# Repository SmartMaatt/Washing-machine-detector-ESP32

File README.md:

<h1 align="center">
    Alarm Amplifier Project
</h1>

<p align="center">
  <a href="#overview">Overview</a> •
  <a href="#hardware">Hardware</a> •
  <a href="#software">Software</a> •
  <a href="#usage-guide">Usage Guide</a> •
  <a href="#testing-and-troubleshooting">Testing and Troubleshooting</a> •
  <a href="#license">License</a>
</p>

## Overview

This project involves the development of an alarm amplifier system designed to monitor the light status of household appliances using photoresistors. It reacts to changes in light with an audio alarm and Bluetooth console notifications. The system is built around the ESP32 microcontroller, incorporating features like Wi-Fi and Bluetooth connectivity.

## Hardware

### Components

- **ESP32 Microcontroller**: Central processing unit of the system, equipped with Wi-Fi and Bluetooth modules.
- **MAX99357 Audio Amplifier**: Converts digital signals into analog sound for the speaker.
- **Photoresistors**: Detects the light status from household appliances.
- **10kOhm Resistors**: Used in conjunction with the photoresistors to create a voltage divider.
- **B3F-1000S Button**: Manual reset button for the alarm system.

*Hardware Components*

### Circuit Diagram

The following is the circuit diagram of the alarm amplifier system:

*Circuit Diagram*

## Software

### Source Code

The project's source code is written in C and utilizes the Arduino IDE for development. Key libraries include:

- `AudioOutputI2S.h`
- `AudioFileSourcePROGMEM.h`
- `AudioGeneratorFLAC.h`
- `BluetoothSerial.h`

### Main Functionalities

- **Initial Setup**: Initializes the system and sets up Bluetooth and audio configurations.
- **Loop Function**: Manages the reading of sensor data, Bluetooth inputs, and alarm triggering.
- **Alarm Management**: Handles the audio alarm based on sensor input and allows manual reset.

### Bluetooth Commands

- `input1`, `input2`, `input3`: Activate/deactivate specific sensors.
- `ShowData`: Display current sensor data and status.
- `stop`: Stop the current alarm.

## Installation and Setup

To install and set up the software on your ESP32 microcontroller, follow these steps:

1. **Software Requirements**:
   - Ensure you have the latest version of the Arduino IDE installed on your computer. It can be downloaded from the [Arduino website](https://www.arduino.cc/en/software).

2. **ESP32 Board Manager Installation**:
   - Open the Arduino IDE.
   - Go to File > Preferences and in the "Additional Board Manager URLs" field, add the following URL: `https://dl.espressif.com/dl/package_esp32_index.json`.
   - Open the Board Manager by going to Tools > Board > Boards Manager, search for ESP32, and install the latest version.

3. **Connect the ESP32 to Your Computer**:
   - Using a micro USB cable, connect the ESP32 to your computer. Ensure that the ESP32 is powered on.

4. **Select the Correct Board and Port**:
   - In the Arduino IDE, go to Tools > Board and select the appropriate ESP32 board (e.g., ESP32 Dev Module).
   - Go to Tools > Port and select the COM port that the ESP32 is connected to.

5. **Load the Software**:
   - Open the project source code in the Arduino IDE.
   - If any additional libraries are required (as mentioned in the Software section), make sure they are installed.

6. **Compile and Upload**:
   - Click the "Upload" button in the Arduino IDE to compile the code and upload it to the ESP32.
   - Wait for the message "Done uploading" to appear in the IDE's console window.

7. **Verify Operation**:
   - After the code is successfully uploaded, the ESP32 should start running the program.
   - Monitor the Serial Monitor in the Arduino IDE for any debug information or confirmation messages.

8. **Bluetooth Pairing**:
   - On your smartphone or Bluetooth-enabled device, turn on Bluetooth and search for new devices.
   - Find the "Washing Machine Detector" and pair with it.
   - Once paired, you can use Bluetooth terminal applications to send commands to the ESP32.

If you encounter any issues during installation, refer to the Troubleshooting section for guidance.

## Usage Guide

To effectively utilize the alarm amplifier system, follow these steps:

1. **Power Connection**: Connect the system to a power source using the micro USB port on the ESP32.
2. **Mounting**: Attach the system near your chosen appliance, ensuring the photoresistors are positioned to accurately detect the appliance's light status.
3. **Bluetooth Connection**: Use a smartphone or computer with Bluetooth to connect to the system. The default Bluetooth name is "Washing Machine Detector".
4. **Sensor Configuration**: Via the Bluetooth terminal, send commands to activate or deactivate the sensors based on your needs. Use `input1`, `input2`, and `input3` commands to control respective sensors.
5. **Monitoring**: The system will now monitor the light signals from the appliance and trigger the alarm when specific conditions are met.
6. **Responding to Alarms**: When the alarm sounds, indicating the completion of an appliance's cycle, you can turn it off using the manual button on the system or through the Bluetooth command `stop`.
7. **Resetting the System**: After stopping the alarm, the system will reset to its initial state with all sensors deactivated. Reactivate the desired sensors to continue monitoring.

## Testing and Troubleshooting

### Testing Process

1. **Functional Testing**: Each component (microcontroller, audio amplifier, photoresistors) was individually tested for functionality before integration.
2. **Integration Testing**: The complete system was tested to ensure all components worked together seamlessly.
3. **Scenario Testing**: Simulated various appliance statuses (light on/off) to test the system's response and the accuracy of sensor readings.
4. **Usability Testing**: Non-technical users tested the system to ensure user-friendliness and ease of setup and operation.
5. **Longevity Testing**: Operated the system over extended periods to ensure durability and consistent performance.

### Troubleshooting

- **Bluetooth Connectivity Issues**: Ensure the device is within range and the ESP32 is powered correctly. Restart the Bluetooth connection if necessary.
- **False Alarms**: Check the positioning of the photoresistors. Ensure they accurately detect the appliance's light without interference from external light sources.
- **System Not Responding**: Verify the power supply and connections. Check for any loose connections in the circuit.

## Conclusions

1. **Functionality**: The system successfully detects the light status from appliances and triggers an alarm, demonstrating effective integration of hardware and software components.
2. **User-Friendly Design**: Testing with non-technical users highlighted the system's user-friendly design and easy setup process.
3. **Challenges Overcome**: Initially faced challenges with integrating sound playback and Bluetooth connectivity. These were resolved through software modifications, improving the system's reliability.
4. **Technical Skills Enhanced**: Gained significant experience in microprocessor systems, circuit design, and practical problem-solving.
5. **Future Improvements**: Potential enhancements include refining the user interface for Bluetooth control and expanding compatibility with a wider range of appliances.

This project has been a comprehensive learning journey, enhancing both technical skills and practical problem-solving abilities in the field of microprocessor systems and IoT applications.

## License
This project is licensed under the MIT License - see the [LICENSE](LICENSE) file for details.

---
&copy; 2023 Mateusz Płonka (SmartMatt). All rights reserved.

<p align="left">
  <a href="https://smartmatt.pl/">Portfolio</a> •
  <a href="https://github.com/SmartMaatt">GitHub</a> •
  <a href="https://www.linkedin.com/in/mateusz-p%C5%82onka-328a48214/">LinkedIn</a> •
  <a href="https://www.youtube.com/user/SmartHDesigner">YouTube</a> •
  <a href="https://www.tiktok.com/@smartmaatt">TikTok</a>
</p>

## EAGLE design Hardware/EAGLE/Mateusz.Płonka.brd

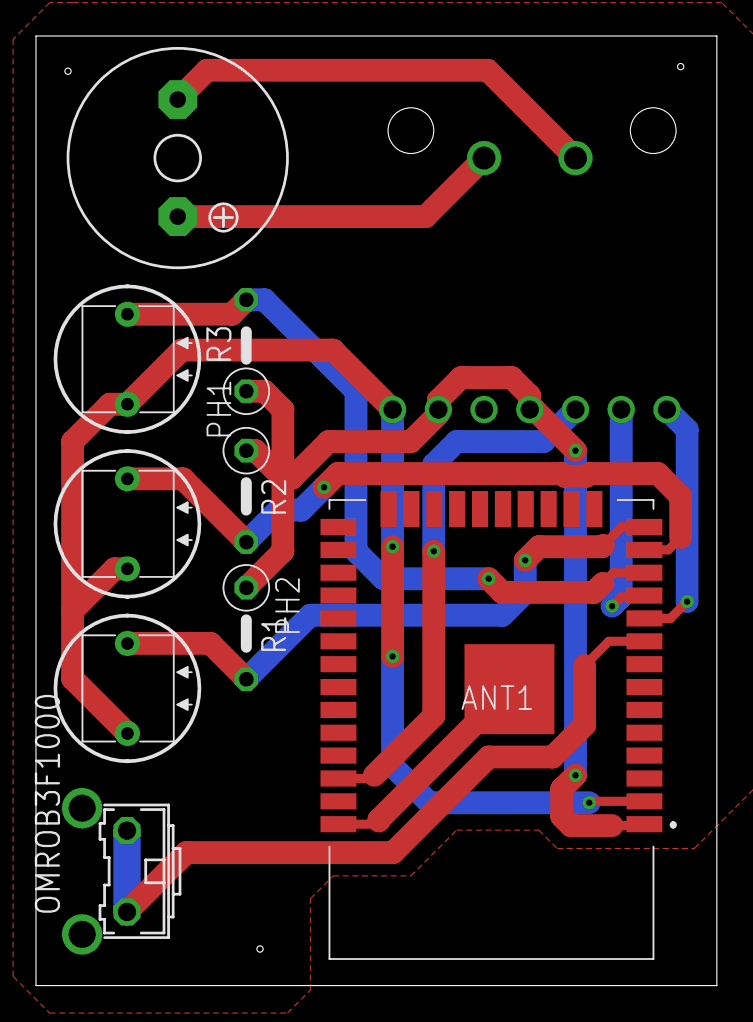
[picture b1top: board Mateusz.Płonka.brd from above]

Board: 2 copper layers, 37.8 x 52.8 mm, 10 parts (1 on the bottom side), 12 nets.

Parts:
ANT1: ESP32-WROOM-32D; ESP32WROOM32D
OMROB3F1000: B3F-31XX
PH1, PH2, PH3: D1160_12; D11XX
R1, R2, R3: 10k; 0207/5V
SP1: KSS1201
U1: KRZYSZTOF.KOCOT_ADAFRUIT-MAX98357-BREAKOUT_MICROBUILDER_QFN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

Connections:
GND: ANT1.1, R1.1, R2.1, R3.1, U1.P$4, U1.P$6
IO12: ANT1.14, PH3.2, R1.2
IO14: ANT1.13, PH2.2, R2.2
IO22: ANT1.36, U1.P$3
IO25: ANT1.10, U1.P$1
IO26: ANT1.11, U1.P$2
IO27: ANT1.12, PH1.2, R3.2
IO33: ANT1.9, OMROB3F1000.1, OMROB3F1000.2
unnamed: SP1.-, U1.P$8
unnamed: SP1.+, U1.P$9
unnamed: ANT1.38, ANT1.39
VCC: ANT1.2, PH1.1, PH2.1, PH3.1, U1.P$7

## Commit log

2021-02-22 v.1 Upload main source code and binary representation
2023-11-11 Hardware and Documentation
2023-11-11 Fixes
2023-11-11 Create LICENSE

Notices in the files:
README.md:
License: MIT
